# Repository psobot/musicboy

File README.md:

# Music Boy
_A high-quality audio playback cartridge for Nintendo® Game Boy® and Game Boy Color®._

(Note: this project is not approved, condoned, or endorsed by Nintendo®.)

## What is _Music Boy_?

_Music Boy_ is a custom hardware cartridge and accompanying software to play
back **high quality audio** on the Nintendo® Game Boy® and Game Boy Color®
handheld game consoles<sup>1</sup>. Music Boy fits in a standard Game Pak®
cartridge casing and requires no additional modifications - it plays like a
standard game.

_Music Boy_ was originally created as a unique distribution mechanism for [PUSHER](https://twitter.com/itspusher)'s [2016 _New Laces_ EP](https://open.spotify.com/album/1mfsE08YoglXSCHUcvpyCJ). While it can be repurposed to work with other Game Boy games, Music Boy currently only plays music in the background of a modified copy of _Super Mario Land_.

> For a more detailed story of _Music Boy_, see [my 2019 talk from !!con: "_Even more vintage: releasing music on a custom-built Game Boy cartridge!_"](https://www.youtube.com/watch?v=5PHLJ7zppfo):
>
> 

<sup>1</sup>_Music Boy_ may work on other consoles, like the Super Game Boy®,
but will not work on the Game Boy Pocket®, Game Boy Advance® or Nintendo DS® due to fundamental
hardware differences.

## How does _Music Boy_ Work?

_Music Boy_ is a highly non-standard cartridge - or rather, a cartridge
_emulator_, built upon an [ARM Cortex-M4](https://en.wikipedia.org/wiki/ARM_Cortex-M#Cortex-M4)
(the STMicroelectronics [STM32F446](https://www.st.com/en/microcontrollers/stm32f446ze.html) family)
system-on-chip. This hardware acts as both a flash emulator, providing the
Game Boy with instructions to execute on its own CPU, and a rudimentary co-processor,
providing the Game Boy with additional facilities and control over
a high-quality analog audio output that can output up to 96kHz at 12 bits.

### Hardware specs

 - CPU: [STM32F446ZET6](https://www.st.com/en/microcontrollers/stm32f446ze.html)
   - ARM Cortex-M4 at 180MHz
   - 512kB Flash Storage (may be a bit overkill)
   - 128kB SRAM
   - 2x 8- or 12-bit DAC channels at sample rates well beyond 96kHz
 - Storage: [W25Q128JV](http://www.winbond.com/resource-files/w25q128jv%20revf%2003272018%20plus.pdf)
   - 128MBit / 16MB Quad-SPI Flash
   - Could use Quad-SPI, but currently only connected in single-SPI mode
   - With 8-bit audio depth, this provides up to ~15 minutes of mono audio at ~14kHz.
     (Unlike most audio hardware, we have granular control over sample rate, and choose the
     sample rate based on the amount of audio we want to fit on the cart.)
   - This could reasonably be replaced with a microSD card for greater storage,
     at a slightly increased per-cartridge part cost
 - Interface: Nintendo Game Pak Connector
   - Pin 31 provides a single mono audio input from the cartridge to the Game Boy®'s audio mixer,
     unused by any commercial games
   - The Game Boy® levels are at 5V, while the STM32F4 outputs 3.3V. Luckily, the Game Boy®
     accepts any voltage above ~2.5V as "high" and the STM32F4 pins are 5V-tolerant.
 - Programmable ST-LINK and SPI Flash headers
   - _Music Boy_ can be debugged or re-flashed _while running in a powered-on Game Boy®_,
     which creates a development experience similar to many modern IDEs.
   - Code loading and debugging is possible via the 5-pin ST-LINK header, which
     requires a corresponding ST-LINK board from STMicroelectronics. (Their line of
     Nucleo boards each come with built-in ST-LINK header boards.)
   - Re-flashing of the flash storage can be accomplished via the 6-pin SPI header,
     which, with a standad SPI programmer (or Raspberry Pi), should be flashed with the contents of `flash.bin`.

### Software

_Music Boy_ uses a combination of software written in C, ARM Assembly, Python, and
Game Boy assembly (a variant of Z80 assembly), all working together in sequence:

 - At compile time, a number of Python scripts generate C and RGBDS assembly code
   to share common variable definitions between the Game Boy and the STM32F4. A
   Python script also prepares a `flash.bin` file that contains all of the audio
   data required for playback, and saves metadata about this binary audio data as
   a C header file for use by the STM32F4.
 - At run time, the STM32F4 CPU starts by:
   - configuring its inputs and outputs appropriately
   - initializing its peripherals (DAC for audio output, DMA for reading audio from Flash)
   - configuring an interrupt handler to trigger every time the Game Boy clock's edge rises
   - pulls the Game Pak `/RST` pin low to force the Game Boy to restart
 - The Game Boy's built-in boot ROM (for [Game Boy](https://gist.github.com/drhelius/6063288) or [Game Boy Color](https://gist.github.com/drhelius/6063265)) then starts to read data from the STM32F4
   - The Game Boy compares the Nintendo logo returned by the STM32F4 to the logo programmed into the Game Boy's ROM. If this logo does not match exactly, the Game Boy halts all execution and prevents the "illegitimate" cartridge from playing.
     - This was a simple form of copy protection, as the Nintendo logo is copyrighted and Nintendo had legal grounds to sue any cartridge maker that included it in a cartridge without the appropriate licence.
   - The Game Boy presents the logo from the cartridge on-screen during boot, then starts reading from the cartridge and executing instructions.
     - Depending on the model, the Game Boy and Game Boy Color perform these operations in different orders. The _Music Boy_ accounts for this and can switch the logo being displayed automatically to present a non-Nintendo logo on the splash screen.
 - Using certain timings obtained during the boot process, the STM32F4 can detect which Game Boy model is currently running the cartridge, and will dynamically patch the software it provides to the Game Boy to run different instructions depending on the model.
   - This is necessary due to slight differences in the audio hardware of each Game Boy model:
     - The Game Boy (DMG, or "Dot Matrix Game") supports anywhere from 0 to 4V on its external audio input (V<sub>in</sub>) pin.
     - The Game Boy Color (CGB, or "Color Game Boy") expects a smaller range of voltages, from 1.9V to 2.5V on its V<sub>in</sub> pin.
 - The STM32F4 maps a region of the Game Boy's address space into its own RAM (4kB, from 0xA000 to 0xAFFF) to allow for communication between the code running on the Game Boy's CPU and code running on the STM32F4.
 - The Game Boy software begins to run a game by treating the STM32F4 as a regular cartridge.
 - The software running on the Game Boy (currently _Super Mario Land_) has been modified by replacing certain instructions:
   - The background music loop no longer plays the original game's music
   - Certain button presses send messages through the shared address space to the STM32F4 (pause and unpause, for instance)
   - Changes in game state or current level are communicated to the STM32F4 through the shared address space
   - The audio hardware is initialized to allow audio pass-through from the STM32F4 to the Game Boy's speaker or headphones
   - Other cosmetic changes (artwork or string changes) to fit the desired application

## Software Installation

Assuming you're on macOS, you'll need:

 - [`brew`](https://brew.sh/)
 - a working Python 2.7 installation (sorry, not Python 3 yet!)
 - a working [gcc_arm installation](https://gist.github.com/joegoggins/7763637)

Then:

```bash
brew install rbgds stlink rsync ffmpeg
pip install -r code/requirements.txt
```

Note that if you want to compile the project completely, you'll need:

 - a copy of the Super Mario Land ROM moved to `code/gbrom/baserom.gb`, with the sha1 `418203621b887caa090215d97e3f509b79affd3e`
 - one or more audio files in the `music` folder, of any format accepted by `ffmpeg`, sorted lexicographically. Each successive file will be used as background music for each level. Note that if you provide more than 9 files, any files after the 9th will not be used.

## Hardware Design

The `hardware` directory contains a [KiCad](http://kicad.org/) project and all of its dependencies.

If you plan to print circuit boards, make sure you use 0.8mm thick PCBs. The PCB dimensions should be 61mm*51.4mm, with a notch on one corner.

If you're not comfortable soldering super-fine-pitch surface mount components (like me) then I recommend using a third-party assembly service such as [Seeed Studio](https://www.seeedstudio.com/prototype-pcb-assembly.html).

## Credits

Music Boy was developed between 2016 and 2019 by [Peter Sobot](https://petersobot.com), but leaned heavily on prior art and help by a number of brilliant people:

 - [dhole](http://dhole.github.io/about/)'s posts on building an STM32 cartridge emulator were extremely helpful:
   - [Emulating a GameBoy Cartridge with an STM32F4. Part 1](https://dhole.github.io/post/gameboy_cartridge_emu_1/) (2014)
   - [Emulating a GameBoy Cartridge with an STM32F4. Part 2](https://dhole.github.io/post/gameboy_cartridge_emu_2/) (2014)
   - [Booting the GameBoy with a custom logo](https://dhole.github.io/post/gameboy_custom_logo/) (2014)
   - [stm32f_GBCart](https://github.com/Dhole/stm32f_GBCart) on GitHub
 - [Anders Granlund](http://www.happydaze.se/)'s post on building a custom Wolfenstein 3D game for Game Boy with a co-processor was super inspiring:
   - [Wolf, Gameboy cartridge with co-processor](http://www.happydaze.se/wolf/) (2016)
 - [Kasper Meerts](https://github.com/kaspermeerts)' disassembly of _Super Mario Land_ (1989) was super useful in providing a game to use as payload
   - [_supermarioland_](https://github.com/kaspermeerts/supermarioland) on GitHub
 - [Eric Evenchick](https://www.evenchick.com/) was instrumental in helping review and validate my hardware design before going to production
 - [PUSHER](https://twitter.com/itspusher), the inspiration for starting this project, was an encouraging patron throughout

## Licenses & Legal

This project is a hacked together custom Game Boy cartridge, based on third-party code,
and - for demoing - using a modified version of a commercial Nintendo game from 1989.

All of my original code and hardware designs in this project are licensed under
[the MIT License](https://en.wikipedia.org/wiki/MIT_License). Some STM32 library files
are licensed with the _MCD-ST Liberty SW License Agreement V2_, as they were
open-sourced by STMicroelectronics, and further helper libraries are licensed by their
own various licenses.

If you're trying to build this yourself, you'll need to supply your own copy of
_Super Mario Land_ and your own audio files. I take no responsibility for any derivative
works created from this project.

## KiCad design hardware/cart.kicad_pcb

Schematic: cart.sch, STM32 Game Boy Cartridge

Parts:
C1: 1uF; C_0603_1608Metric_Pad1.05x0.95mm_HandSolder
C2, C4, C5, C6, C7: 100nF; C_0603_1608Metric_Pad1.05x0.95mm_HandSolder
C3: 470pF; C_0402
C9, C10, C11: 2.2uF; C_0603
CP1: 47uF; CP_Tantalum_Case-A_EIA-3216-18_Hand
J1: Game Boy GamePak Connector; GameBoy_Cartridge_1x32_P1.50mm_Edge
R1: 10k; R_0603_HandSoldering
SPIHDR1: for flashing audio; 1X06_LOCK
SWDHDR1: for flashing code; 1X05_LOCK
U1: STM32F446ZETx; LQFP-144_20x20mm_P0.5mm
U2: MIC5219-3.3; SOT-23-5
U3: W25Q128JVSIQ; SOIC-8_3.9x4.9mm_P1.27mm

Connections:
+3V3: C4.2, C5.2, C6.2, C7.2, C11.2, SPIHDR1.1, SWDHDR1.1, U1.6 (VBAT), U1.17 (VDD), U1.30 (VDD), U1.32 (VREF+), U1.33 (VDDA), U1.39 (VDD), U1.52 (VDD), U1.62 (VDD), U1.72 (VDD), U1.84 (VDD), U1.95 (VDDUSB), U1.108 (VDD), U1.121 (VDD), U1.131 (VDD), U1.143 (PDR_ON), U1.144 (VDD), U2.5 (OUT), U3.8
+5V: C1.1, C2.1, J1.1, U2.1 (IN), U2.3 (EN)
GBADDR0: J1.6, U1.114 (PD0)
GBADDR1: J1.7, U1.115 (PD1)
GBADDR2: J1.8, U1.116 (PD2)
GBADDR3: J1.9, U1.117 (PD3)
GBADDR4: J1.10, U1.118 (PD4)
GBADDR5: J1.11, U1.119 (PD5)
GBADDR6: J1.12, U1.122 (PD6)
GBADDR7: J1.13, U1.123 (PD7)
GBADDR8: J1.14, U1.98 (PC8)
GBADDR9: J1.15, U1.99 (PC9)
GBADDR10: J1.16, U1.111 (PC10)
GBADDR11: J1.17, U1.112 (PC11)
GBADDR12: J1.18, U1.81 (PD12)
GBADDR13: J1.19, U1.82 (PD13)
GBADDR14: J1.20, U1.85 (PD14)
GBADDR15: J1.21, U1.86 (PD15)
GBCLK: J1.2, U1.26 (PC0)
GBDATA0: J1.22, U1.59 (PE8)
GBDATA1: J1.23, U1.60 (PE9)
GBDATA2: J1.24, U1.63 (PE10)
GBDATA3: J1.25, U1.64 (PE11)
GBDATA4: J1.26, U1.65 (PE12)
GBDATA5: J1.27, U1.66 (PE13)
GBDATA6: J1.28, U1.67 (PE14)
GBDATA7: J1.29, U1.68 (PE15)
GBREAD: J1.4, U1.28 (PC2)
GBRESET: J1.30, U1.56 (PG0)
GBWRITE: J1.3, U1.29 (PC3)
NRST: SWDHDR1.5, U1.25 (NRST)
unnamed: C3.1, U2.4 (BP)
unnamed: C9.1, U1.106 (VCAP_2)
unnamed: C10.1, U1.71 (VCAP_1)
unnamed: CP1.1, U1.40 (PA4)
SPI_CLK: SPIHDR1.2, U1.41 (PA5), U3.6
SPI_CS: SPIHDR1.3, U1.133 (PB3), U3.1
SPI_DI: SPIHDR1.4, U1.43 (PA7), U3.5
SPI_DO: SPIHDR1.5, U1.42 (PA6), U3.2
SWDCLK: SWDHDR1.2, U1.109 (PA14)
SWDIO: SWDHDR1.4, U1.105 (PA13)
VIN: CP1.2, J1.31, R1.2

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
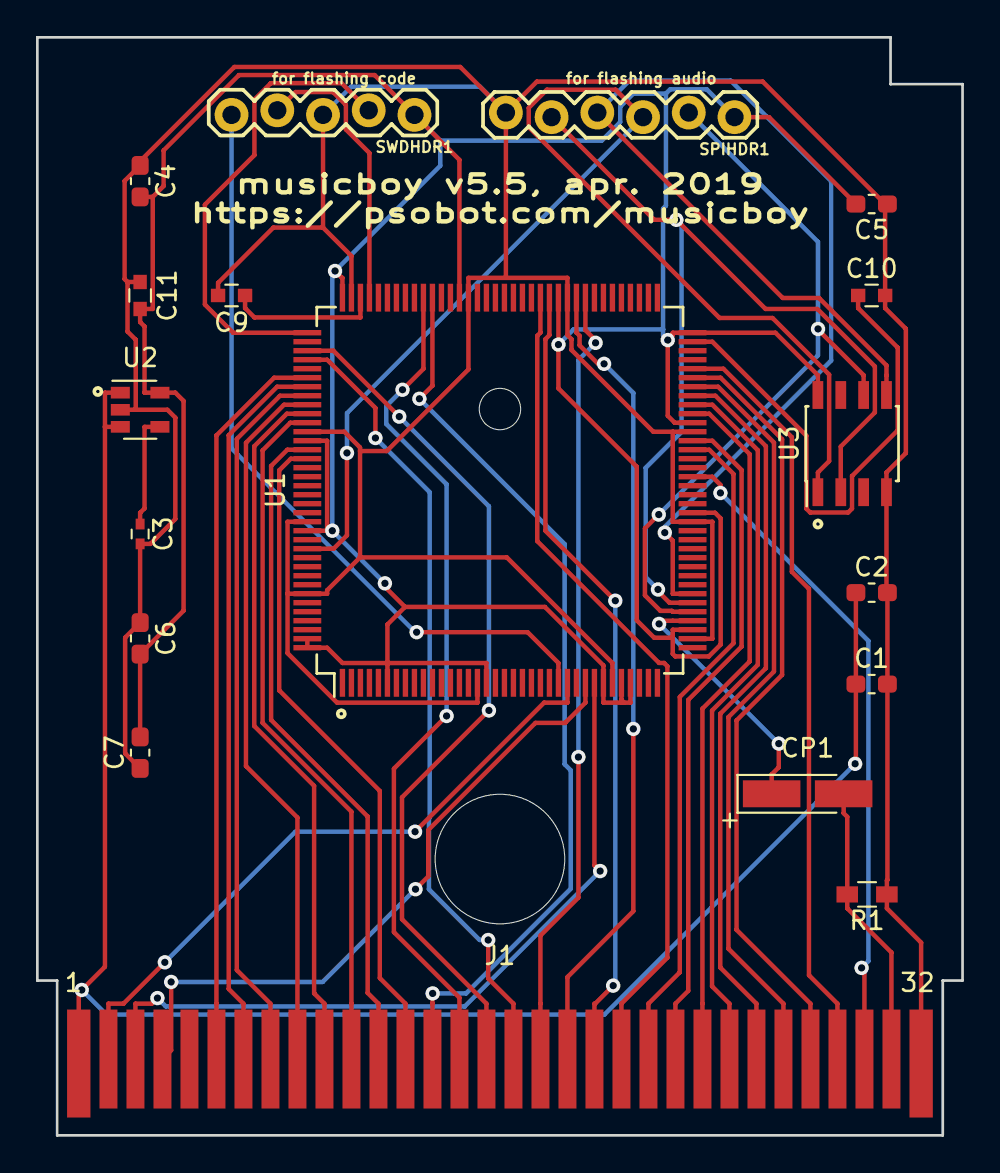
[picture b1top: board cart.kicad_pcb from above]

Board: 2 copper layers, 51.4 x 61.0 mm, 20 parts (0 on the bottom side), 43 nets.

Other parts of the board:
MK1: DNF; MountingHole_7.2mm
MK2: DNF; MountingHole_2.3mm

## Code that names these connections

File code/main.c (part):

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
extern uint8_t rom_bank;

/* Configure GPIO PC0 to trigger interrupt on rise */
void configure_clock_interrupt(void) {
  EXTI_InitTypeDef EXTI_InitStruct;
  NVIC_InitTypeDef NVIC_InitStruct;
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  /* Enable clock for SYSCFG */
  RCC_APB2PeriphClockCmd(RCC_APB2Periph_SYSCFG, ENABLE);

  /* Tell system that you will use PC0 for EXTI_Line0 */
  SYSCFG_EXTILineConfig(EXTI_PortSourceGPIOC, EXTI_PinSource0);

  /* PC0 is connected to EXTI_Line0 */
  EXTI_InitStruct.EXTI_Line = EXTI_Line0;
  /* Enable interrupt */
  EXTI_InitStruct.EXTI_LineCmd = ENABLE;
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  EXTI_Init(&EXTI_InitStruct);

  /* Add IRQ vector to NVIC */
  /* PC0 is connected to EXTI_Line0, which has EXTI0_IRQn vector */
  NVIC_InitStruct.NVIC_IRQChannel = EXTI0_IRQn;
  /* Set priority */
  NVIC_InitStruct.NVIC_IRQChannelPreemptionPriority = 0x00;
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  NVIC_Init(&NVIC_InitStruct);
}

/* Input Signals GPIO pins on CLK -> PC0, RD -> PC2, WR -> PC3 */
void config_gpio_sig(void) {
  /* GPIOC Periph clock enable */
  RCC_AHB1PeriphClockCmd(RCC_AHB1Periph_GPIOC, ENABLE);
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void reset_gb(void) {
  RCC_AHB1PeriphClockCmd(RCC_AHB1Periph_GPIOG, ENABLE);

  // Pull PG0 to ground briefly to reset the Game Boy.

  GPIO_InitStructure.GPIO_Pin = GPIO_Pin_0;
  GPIO_InitStructure.GPIO_Mode = GPIO_Mode_OUT;
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
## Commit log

2019-07-21 Initial public commit.
2019-11-02 Bump pillow from 4.2.0 to 6.2.0 in /code
    Bumps [pillow](https://github.com/python-pillow/Pillow) from 4.2.0 to 6.2.0.
    - [Release notes](https://github.com/python-pillow/Pillow/releases)
    - [Changelog](https://github.com/python-pillow/Pillow/blob/master/CHANGES.rst)
    - [Commits](https://github.com/python-pillow/Pillow/compare/4.2.0...6.2.0)
2021-03-19 Bump pillow from 4.2.0 to 8.1.1 in /code
    Bumps [pillow](https://github.com/python-pillow/Pillow) from 4.2.0 to 8.1.1.
    - [Release notes](https://github.com/python-pillow/Pillow/releases)
    - [Changelog](https://github.com/python-pillow/Pillow/blob/master/CHANGES.rst)
    - [Commits](https://github.com/python-pillow/Pillow/compare/4.2.0...8.1.1)
2021-06-08 Bump pillow from 4.2.0 to 8.2.0 in /code
    Bumps [pillow](https://github.com/python-pillow/Pillow) from 4.2.0 to 8.2.0.
    - [Release notes](https://github.com/python-pillow/Pillow/releases)
    - [Changelog](https://github.com/python-pillow/Pillow/blob/master/CHANGES.rst)
    - [Commits](https://github.com/python-pillow/Pillow/compare/4.2.0...8.2.0)
    ---
    updated-dependencies:
2021-09-08 Bump pillow from 4.2.0 to 8.3.2 in /code
    Bumps [pillow](https://github.com/python-pillow/Pillow) from 4.2.0 to 8.3.2.
    - [Release notes](https://github.com/python-pillow/Pillow/releases)
    - [Changelog](https://github.com/python-pillow/Pillow/blob/master/CHANGES.rst)
    - [Commits](https://github.com/python-pillow/Pillow/compare/4.2.0...8.3.2)
    ---
    updated-dependencies:
2021-11-10 Update README.md
    https://forum.kicad.info/t/warning-avoid-all-links-to-kicad-pcb-org-use-kicad-org/31521
2022-01-13 Bump pillow from 4.2.0 to 9.0.0 in /code
    Bumps [pillow](https://github.com/python-pillow/Pillow) from 4.2.0 to 9.0.0.
    - [Release notes](https://github.com/python-pillow/Pillow/releases)
    - [Changelog](https://github.com/python-pillow/Pillow/blob/main/CHANGES.rst)
    - [Commits](https://github.com/python-pillow/Pillow/compare/4.2.0...9.0.0)
    ---
    updated-dependencies:
2022-03-11 Bump pillow from 4.2.0 to 9.0.1 in /code
    Bumps [pillow](https://github.com/python-pillow/Pillow) from 4.2.0 to 9.0.1.
    - [Release notes](https://github.com/python-pillow/Pillow/releases)
    - [Changelog](https://github.com/python-pillow/Pillow/blob/main/CHANGES.rst)
    - [Commits](https://github.com/python-pillow/Pillow/compare/4.2.0...9.0.1)
    ---
    updated-dependencies:
2022-11-22 Bump pillow from 4.2.0 to 9.3.0 in /code
    Bumps [pillow](https://github.com/python-pillow/Pillow) from 4.2.0 to 9.3.0.
    - [Release notes](https://github.com/python-pillow/Pillow/releases)
    - [Changelog](https://github.com/python-pillow/Pillow/blob/main/CHANGES.rst)
    - [Commits](https://github.com/python-pillow/Pillow/compare/4.2.0...9.3.0)
    ---
    updated-dependencies:
2023-10-03 Bump pillow from 4.2.0 to 10.0.1 in /code
    Bumps [pillow](https://github.com/python-pillow/Pillow) from 4.2.0 to 10.0.1.
    - [Release notes](https://github.com/python-pillow/Pillow/releases)
    - [Changelog](https://github.com/python-pillow/Pillow/blob/main/CHANGES.rst)
    - [Commits](https://github.com/python-pillow/Pillow/compare/4.2.0...10.0.1)
    ---
    updated-dependencies:
